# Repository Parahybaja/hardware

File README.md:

# Hardware v2

<p align="center">

</p>

<p align="center">

</p>

## UECU

Universal Electronics Control Unit

## Module

The Accelaration and Velocity test module

### Signal Cleaning

A signal cleaning stage was employed in the digital inputs of each sensor with the aim of eliminating electromagnetic interference in the data transmission line. For this purpose, a passive low-pass filter with a cutoff frequency of 1GHz was implemented.

To achieve the desired cutoff frequency, based on a resistor of *2.2k* ohms, chosen to maintain the optimal current for the optocoupler's LED, the following calculations were made:

$$
F_c = \frac{1}{{2 \pi R C}}
$$

$$
C = \frac{1}{{F_c \cdot 2 \pi R}}
$$

$$
C = \frac{1}{{1 \text{GHz} \cdot 2 \pi \cdot 2.2k}}
$$

$$
C \approx 72 \text{pF}
$$

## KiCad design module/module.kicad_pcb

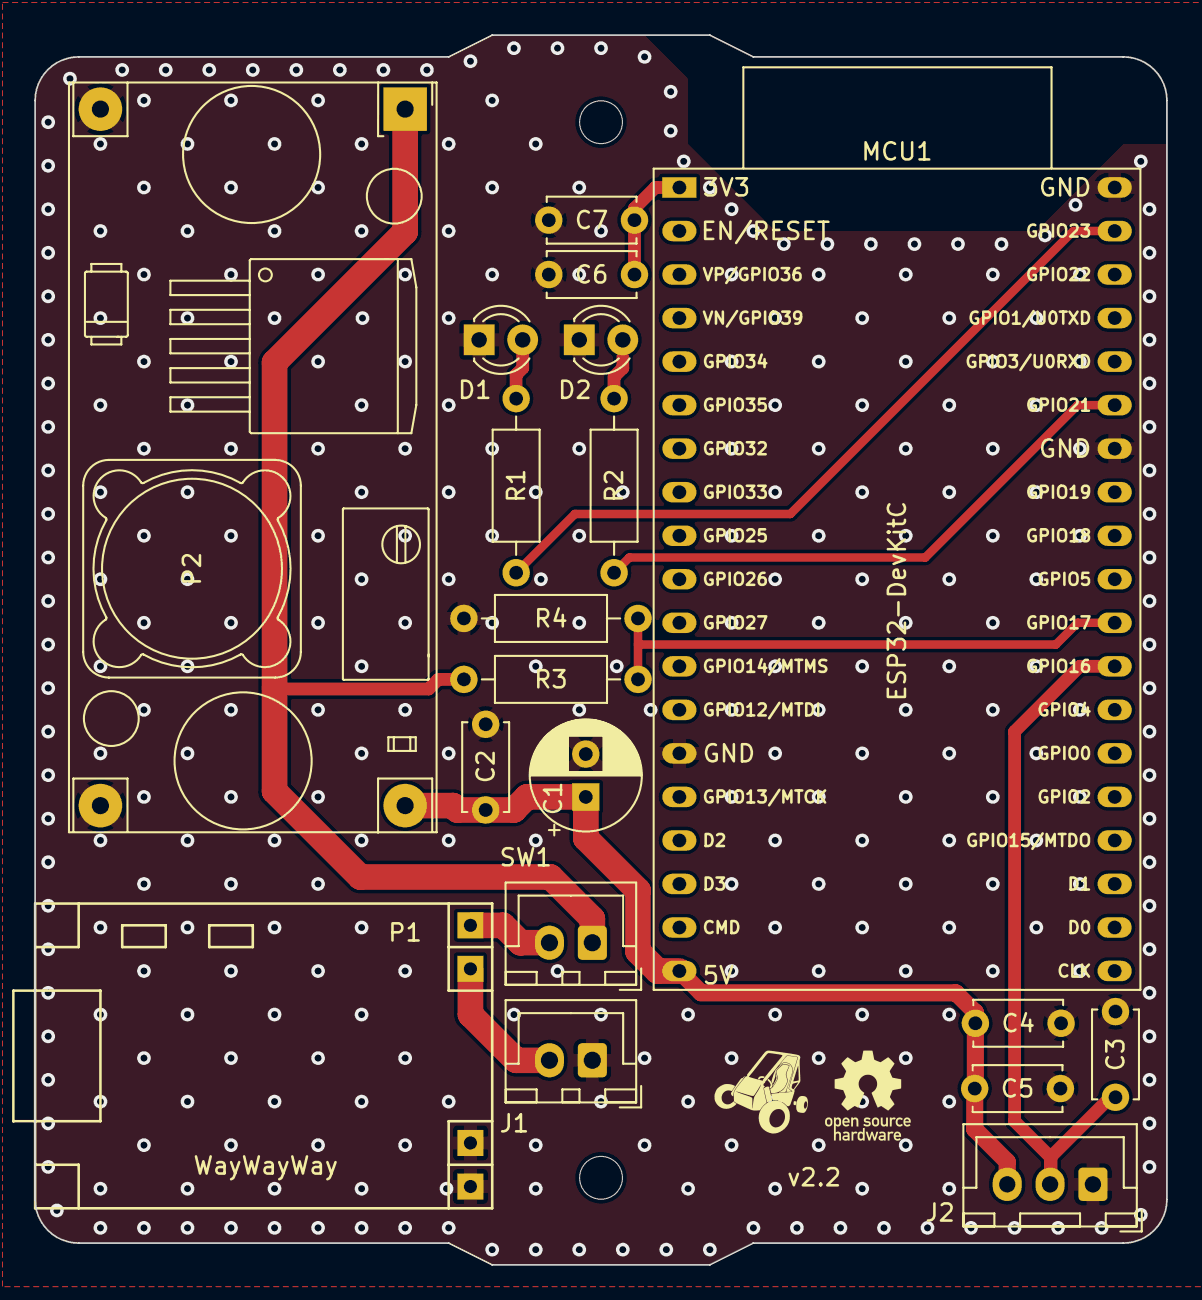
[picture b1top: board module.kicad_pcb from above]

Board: 2 copper layers, 66.0 x 71.8 mm, 23 parts (0 on the bottom side), 12 nets.

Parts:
C1: 470uF; CP_Radial_D6.3mm_P2.50mm
C2, C5, C7: 100nF; C_Disc_D5.0mm_W2.5mm_P5.00mm
C3: 22pF; C_Disc_D5.0mm_W2.5mm_P5.00mm
C4, C6: 10uF; C_Disc_D5.0mm_W2.5mm_P5.00mm
D1: LEDR; LED_D3.0mm
D2: LEDG; LED_D3.0mm
H1, H2: 3.7; MountingHole_3.7mm
J1: Conn_bat; JST_XH_B2B-XH-A_1x02_P2.50mm_Vertical
J2: Conn_bat; JST_XH_B3B-XH-A_1x03_P2.50mm_Vertical
L1: parahybaja
L2: open_hardware
MCU1: ESP32-DevKitC
P1: TP4056 with protection; TP4056
P2: step up boost; StepDown_LM2596
R1, R2: 300R; R_Axial_DIN0207_L6.3mm_D2.5mm_P10.16mm_Horizontal
R3, R4: R_Small; R_Axial_DIN0207_L6.3mm_D2.5mm_P10.16mm_Horizontal
SW1: Conn_sw; JST_XH_B2B-XH-A_1x02_P2.50mm_Vertical

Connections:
+3V3: C6.1, C7.1, MCU1.1 (3V3)
+5V: C1.1, C2.1, C4.1, C5.1, J2.3, MCU1.19 (5V), P2.4 (Vout)
GND: C1.2, C2.2, C3.2, C4.2, C5.2, C6.2, C7.2, D1.1 (K), D2.1 (K), J1.1, J2.1, MCU1.14 (GND), MCU1.32 (GND), MCU1.38 (GND), P1.3 (B-), P1.4 (OUT-), P2.2 (GND), P2.3 (GND), R4.2
LED_ALIVE: MCU1.37 (GPIO23), R1.1
LED_ON: MCU1.33 (GPIO21), R2.1
unnamed: D1.2 (A), R1.2
unnamed: D2.2 (A), R2.2
unnamed: J1.2, P1.2 (B+)
unnamed: P1.1 (OUT+), SW1.2 (B)
VBat: P2.1 (Vin), R3.1, SW1.1 (A)
VOLTAGE_DIVIDER: MCU1.28 (GPIO17), R3.2, R4.1
signal: C3.1, J2.2, MCU1.27 (GPIO16)

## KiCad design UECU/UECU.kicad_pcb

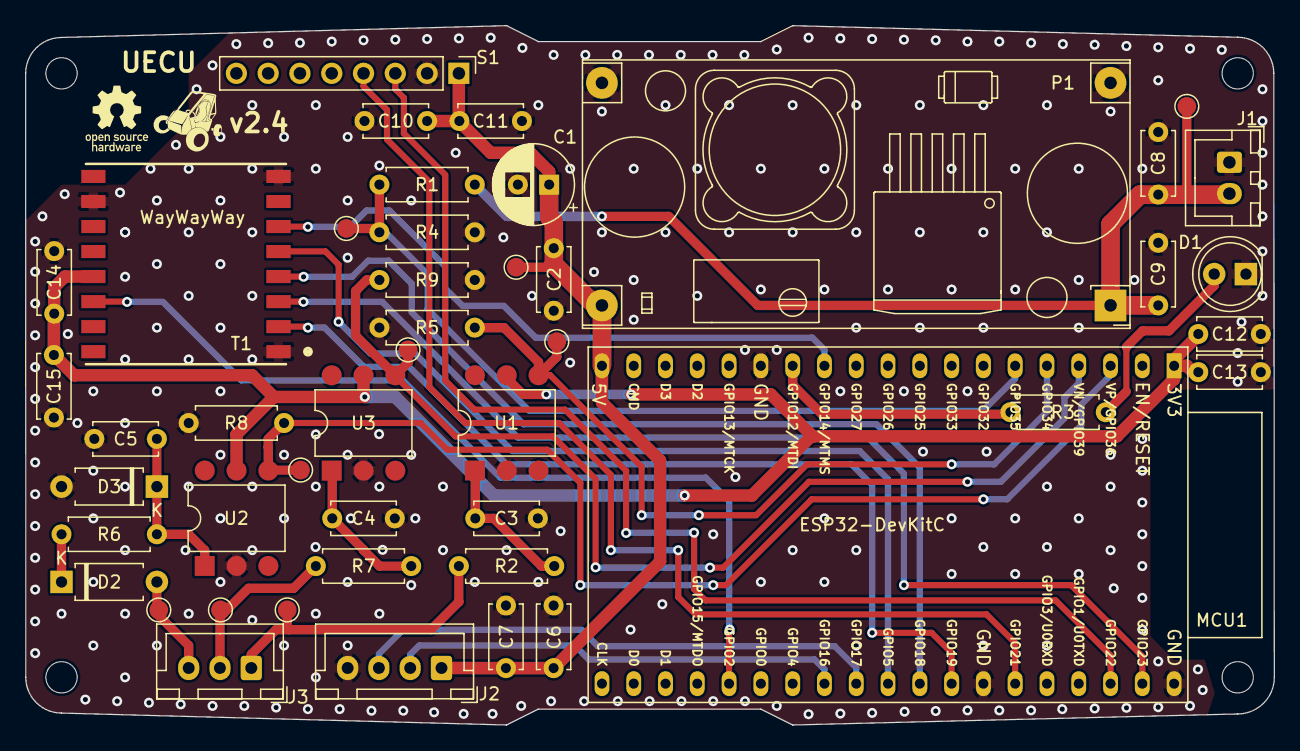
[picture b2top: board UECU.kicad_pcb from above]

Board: 2 copper layers, 99.8 x 55.9 mm, 44 parts (0 on the bottom side), 27 nets.

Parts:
C1: 470uF; CP_Radial_D6.3mm_P2.50mm
C2, C7, C9, C11, C13, C15: 100nF; C_Disc_D5.0mm_W2.5mm_P5.00mm
C3, C4, C5: 10pF; C_Disc_D5.0mm_W2.5mm_P5.00mm
C6, C8, C10, C12, C14: 10uF; C_Disc_D5.0mm_W2.5mm_P5.00mm
D1: LED; LED_D5.0mm
D2: 1N4007; D_A-405_P7.62mm_Horizontal
D3: ZENER 3V3; D_A-405_P7.62mm_Horizontal
H1, H2, H3, H4: 3.7; MountingHole_3.7mm
J1: Conn_pwr; JST_XH_B2B-XH-A_1x02_P2.50mm_Vertical
J2: Conn_display; JST_XH_B4B-XH-A_1x04_P2.50mm_Vertical
J3: Conn_SENSORS; JST_XH_B3B-XH-A_1x03_P2.50mm_Vertical
L1: parahybaja
L2: open_hardware
MCU1: ESP32-DevKitC
P1: LM2596_buck; StepDown_LM2596
R1, R5, R8, R9: 10k; R_Axial_DIN0207_L6.3mm_D2.5mm_P7.62mm_Horizontal
R2, R7: 2k; R_Axial_DIN0207_L6.3mm_D2.5mm_P7.62mm_Horizontal
R3: 470R; R_Axial_DIN0207_L6.3mm_D2.5mm_P7.62mm_Horizontal
R4: 2k2; R_Axial_DIN0207_L6.3mm_D2.5mm_P7.62mm_Horizontal
R6: 59k; R_Axial_DIN0207_L6.3mm_D2.5mm_P7.62mm_Horizontal
REFe: TestPoint_Pad_D1.5mm
S1: PinHeader_1x08_P2.54mm_Vertical
T1: LoRa-SX1276; LoRa_SX1276
U1, U2, U3: 4N25; DIP-6_W7.62mm

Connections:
+3V3: C12.1, C13.1, C14.1, C15.1, MCU1.1 (3V3), T1.13 (3_3V), U1.5, U2.5, U3.5
+5V: C1.1, C2.1, C6.1, C7.1, C10.1, C11.1, J2.1, MCU1.19 (5V), P1.4 (Vout), S1.1 (VCC)
+12V: C8.1, C9.1, J1.2, P1.1 (Vin), R1.1
CONN_EMG: J3.1, R2.1
CONN_RPM: D2.2 (A), J3.3
CONN_SPD: J3.2, R7.1, REFe.1
DIO: MCU1.24 (*GPIO2/ADC2_CH2), T1.14 (DIO0)
GND: C1.2, C2.2, C3.2, C4.2, C5.2, C6.2, C7.2, C8.2, C9.2, C10.2, C11.2, C12.2, C13.2, C14.2, C15.2, D1.1 (K), D3.2 (A), J1.1, J2.4, MCU1.14 (GND), MCU1.32 (GND), MCU1.38 (GND), P1.2 (GND), P1.3 (GND), R4.2, R5.2, R8.2, R9.2, S1.2 (GND), T1.1 (GND), T1.8 (GND), T1.10 (GND), U1.2, U2.2, U3.2
LED_ALIVE: MCU1.13 (VDD_FLASH/GPIO12/*MTDI/ADC2_CH5), R3.1
MISO: MCU1.31 (GPIO19), T1.2 (MISO)
MOSI: MCU1.37 (GPIO23), T1.3 (MOSI)
NSS: MCU1.29 (SDIO/*GPIO5), T1.5 (NSS)
unnamed: C3.1, R2.2, U1.1
unnamed: C4.1, R7.2, U3.1
unnamed: D1.2 (A), R3.2
unnamed: D2.1 (K), R6.1
unnamed: C5.1, D3.1 (K), R6.2, U2.1
RST: MCU1.12 (GPIO14/MTMS/ADC2_CH6), T1.6 (RESET)
RXD2: J2.2, MCU1.27 (GPIO16)
SCK: MCU1.30 (GPIO18), T1.4 (SCK)
SCL: MCU1.36 (GPIO22), S1.3 (SCL)
SDA: MCU1.33 (GPIO21), S1.4 (SDA)
SIGNAL_EMG: MCU1.5 (GPIO34/VDET_1/ADC1_CH6), R5.1, U1.4
SIGNAL_RPM: MCU1.3 (GPIO36/SENSOR_VP/ADC1_CH0), R8.1, U2.4
SIGNAL_SPD: MCU1.4 (GPIO39/SENSOR_VN/ADC1_CH3), R9.1, U3.4
TXD2: J2.3, MCU1.28 (GPIO17)
VBAT-3V: MCU1.6 (GPIO35/VDET_2/ADC1_CH7), R1.2, R4.1

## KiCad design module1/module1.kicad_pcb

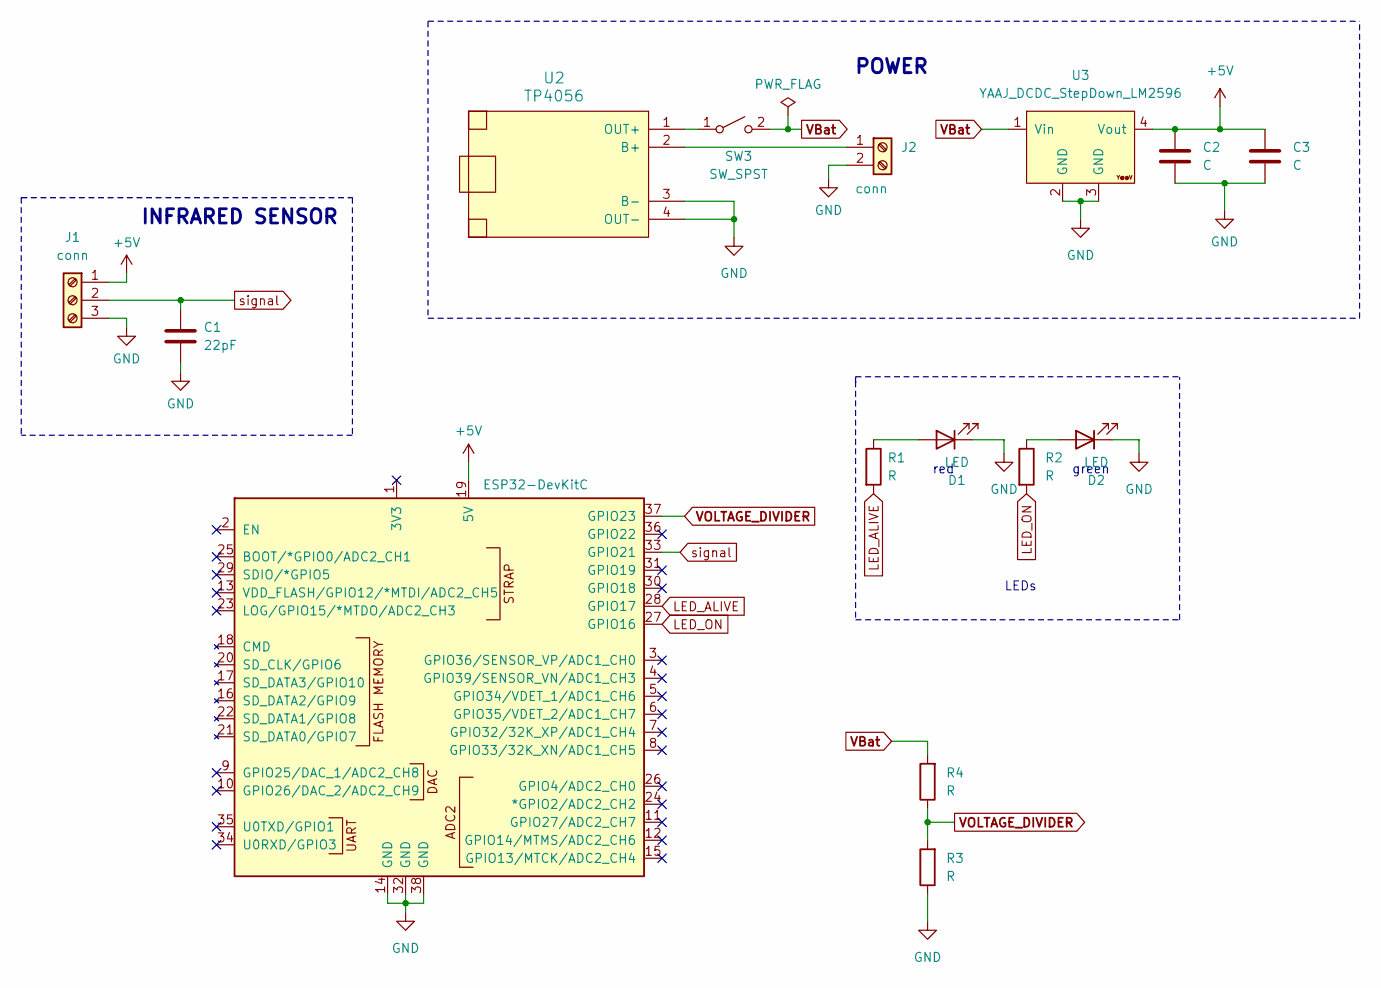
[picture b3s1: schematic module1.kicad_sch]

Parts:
C1: 22pF; C_Disc_D3.0mm_W1.6mm_P2.50mm
C2, C3: C; C_Disc_D3.0mm_W1.6mm_P2.50mm
D1, D2: LED; LED_D3.0mm
J1: conn; TerminalBlock_bornier-3_P5.08mm
J2: conn; TerminalBlock_bornier-2_P5.08mm
R1, R2, R3, R4: R; R_Axial_DIN0207_L6.3mm_D2.5mm_P10.16mm_Horizontal
SW3: SW_SPST; TerminalBlock_bornier-2_P5.08mm
U1: ESP32-DevKitC
U2: TP4056
U3: YAAJ_DCDC_StepDown_LM2596; StepDown_LM2596

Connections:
+5V: C2.1, C3.1, J1.1, U1.19 (5V), U3.4 (Vout)
GND: C1.2, C2.2, C3.2, D1.1 (K), D2.1 (K), J1.3, J2.2, R3.1, U1.14 (GND), U1.32 (GND), U1.38 (GND), U2.3 (B-), U2.4 (OUT-), U3.2 (GND), U3.3 (GND)
LED_ALIVE: R1.2, U1.28 (GPIO17)
LED_ON: R2.2, U1.27 (GPIO16)
unnamed: D1.2 (A), R1.1
unnamed: D2.2 (A), R2.1
unnamed: J2.1, U2.2 (B+)
unnamed: SW3.1 (A), U2.1 (OUT+)
VBat: R4.2, SW3.2 (B), U3.1 (Vin)
VOLTAGE_DIVIDER: R3.2, R4.1, U1.37 (GPIO23)
signal: C1.1, J1.2, U1.33 (GPIO21)

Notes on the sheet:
INFRARED SENSOR
LEDs
red
POWER
green

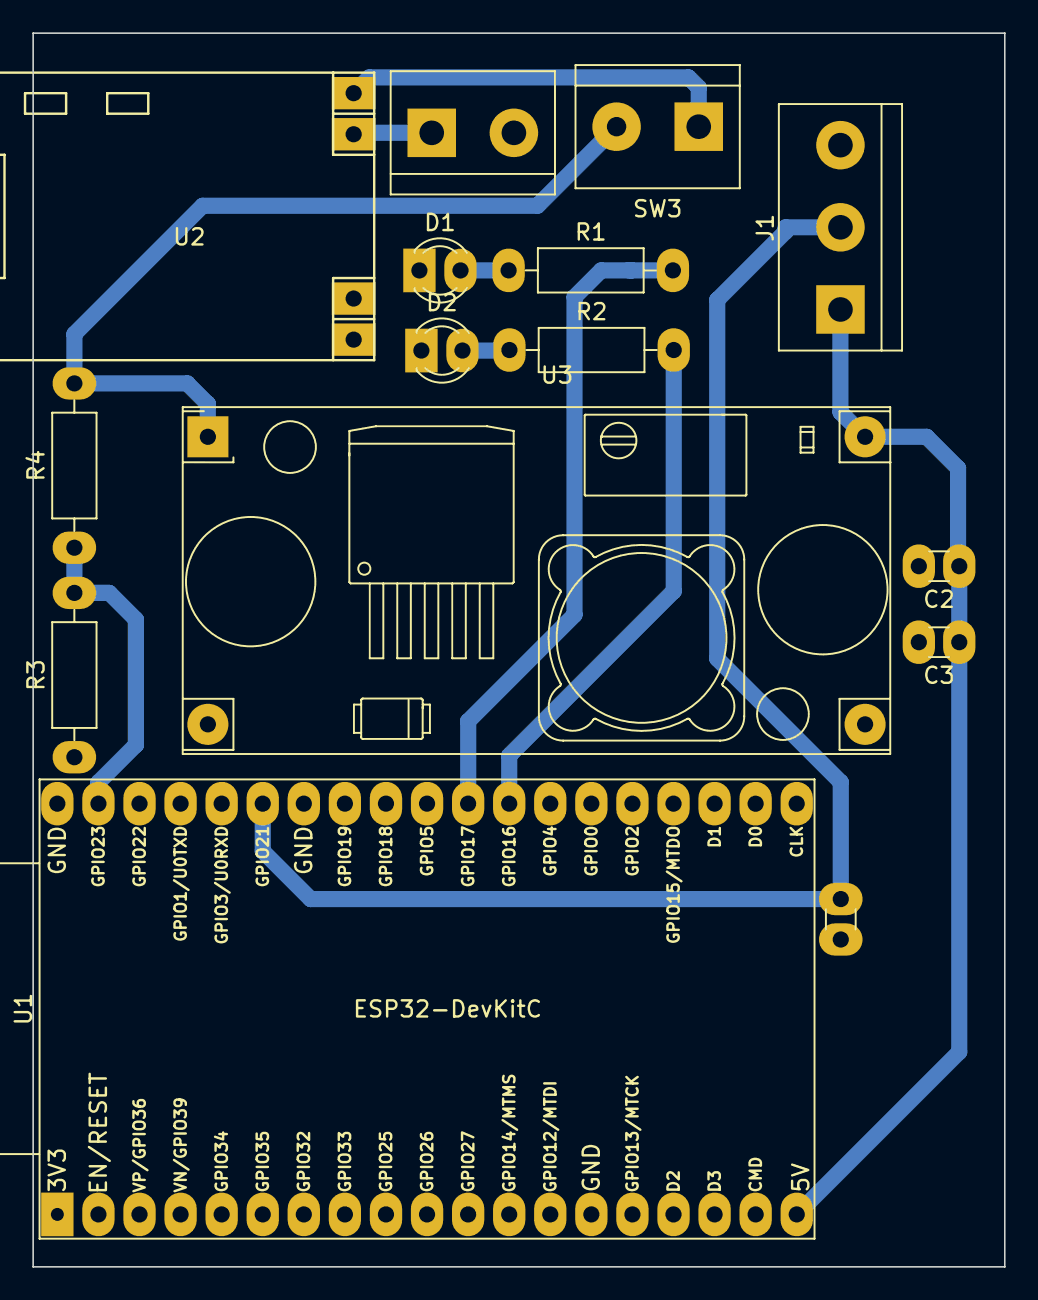
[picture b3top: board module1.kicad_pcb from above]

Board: 2 copper layers, 60.1 x 76.3 mm, 16 parts (1 on the bottom side), 11 nets.

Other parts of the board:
e: LOGO; logocarro

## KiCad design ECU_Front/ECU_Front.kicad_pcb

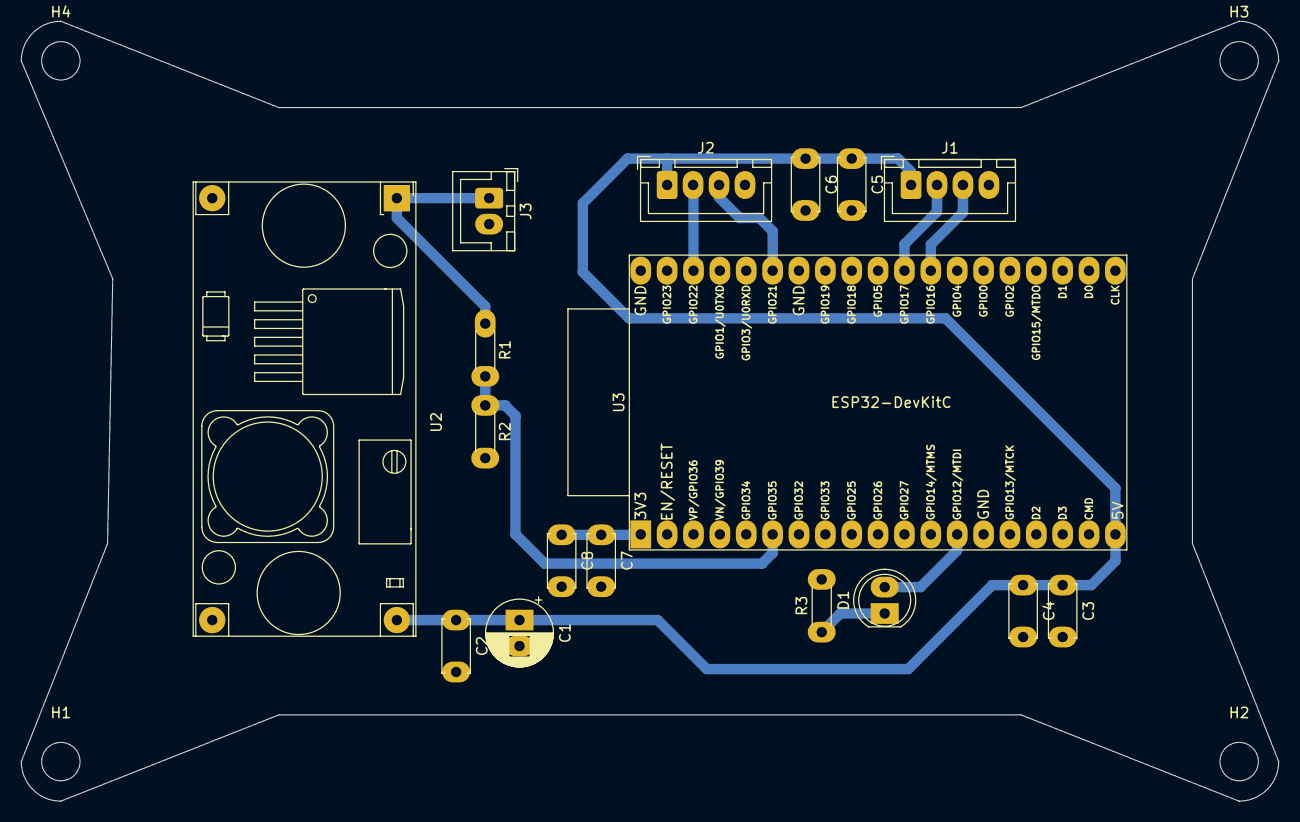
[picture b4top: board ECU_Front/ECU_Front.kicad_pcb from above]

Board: 2 copper layers, 121.1 x 75.1 mm, 21 parts (0 on the bottom side), 11 nets.

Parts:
C1: 470uF; CP_Radial_D6.3mm_P2.50mm
C2, C4, C6, C8: 100nF; C_Disc_D5.0mm_W2.5mm_P5.00mm
C3, C5, C7: 10uF; C_Disc_D5.0mm_W2.5mm_P5.00mm
D1: LED; LED_D5.0mm
H1, H2, H3, H4: 3.7; MountingHole_3.7mm
J1: Conn_display; JST_XH_B4B-XH-A_1x04_P2.50mm_Vertical
J2: Conn_acc; JST_XH_B4B-XH-A_1x04_P2.50mm_Vertical
J3: Conn_pwr; JST_XH_B2B-XH-A_1x02_P2.50mm_Vertical
R1: 10k; R_Axial_DIN0204_L3.6mm_D1.6mm_P5.08mm_Horizontal
R2: 2k2; R_Axial_DIN0204_L3.6mm_D1.6mm_P5.08mm_Horizontal
R3: 470R; R_Axial_DIN0204_L3.6mm_D1.6mm_P5.08mm_Horizontal
U2: LM2596_buck; StepDown_LM2596
U3: ESP32-DevKitC

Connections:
+3V3: C7.1, C8.1, U3.1 (3V3)
+5V: C1.1, C2.1, C3.1, C4.1, C5.1, C6.1, J1.1, J2.1, U2.4 (Vout), U3.19 (5V)
+12V: J3.1, R1.1, U2.1 (Vin)
GND: C1.2, C2.2, C3.2, C4.2, C5.2, C6.2, C7.2, C8.2, J1.4, J2.4, J3.2, R2.2, R3.2, U2.2 (GND), U2.3 (GND), U3.14 (GND), U3.32 (GND), U3.38 (GND)
LED_ALIVE: D1.2 (A), U3.13 (VDD_FLASH/GPIO12/*MTDI/ADC2_CH5)
unnamed: D1.1 (K), R3.1
RXD2: J1.3, U3.27 (GPIO16)
SCL: J2.2, U3.36 (GPIO22)
SDA: J2.3, U3.33 (GPIO21)
TXD2: J1.2, U3.28 (GPIO17)
VBAT-3V: R1.2, R2.1, U3.6 (GPIO35/VDET_2/ADC1_CH7)

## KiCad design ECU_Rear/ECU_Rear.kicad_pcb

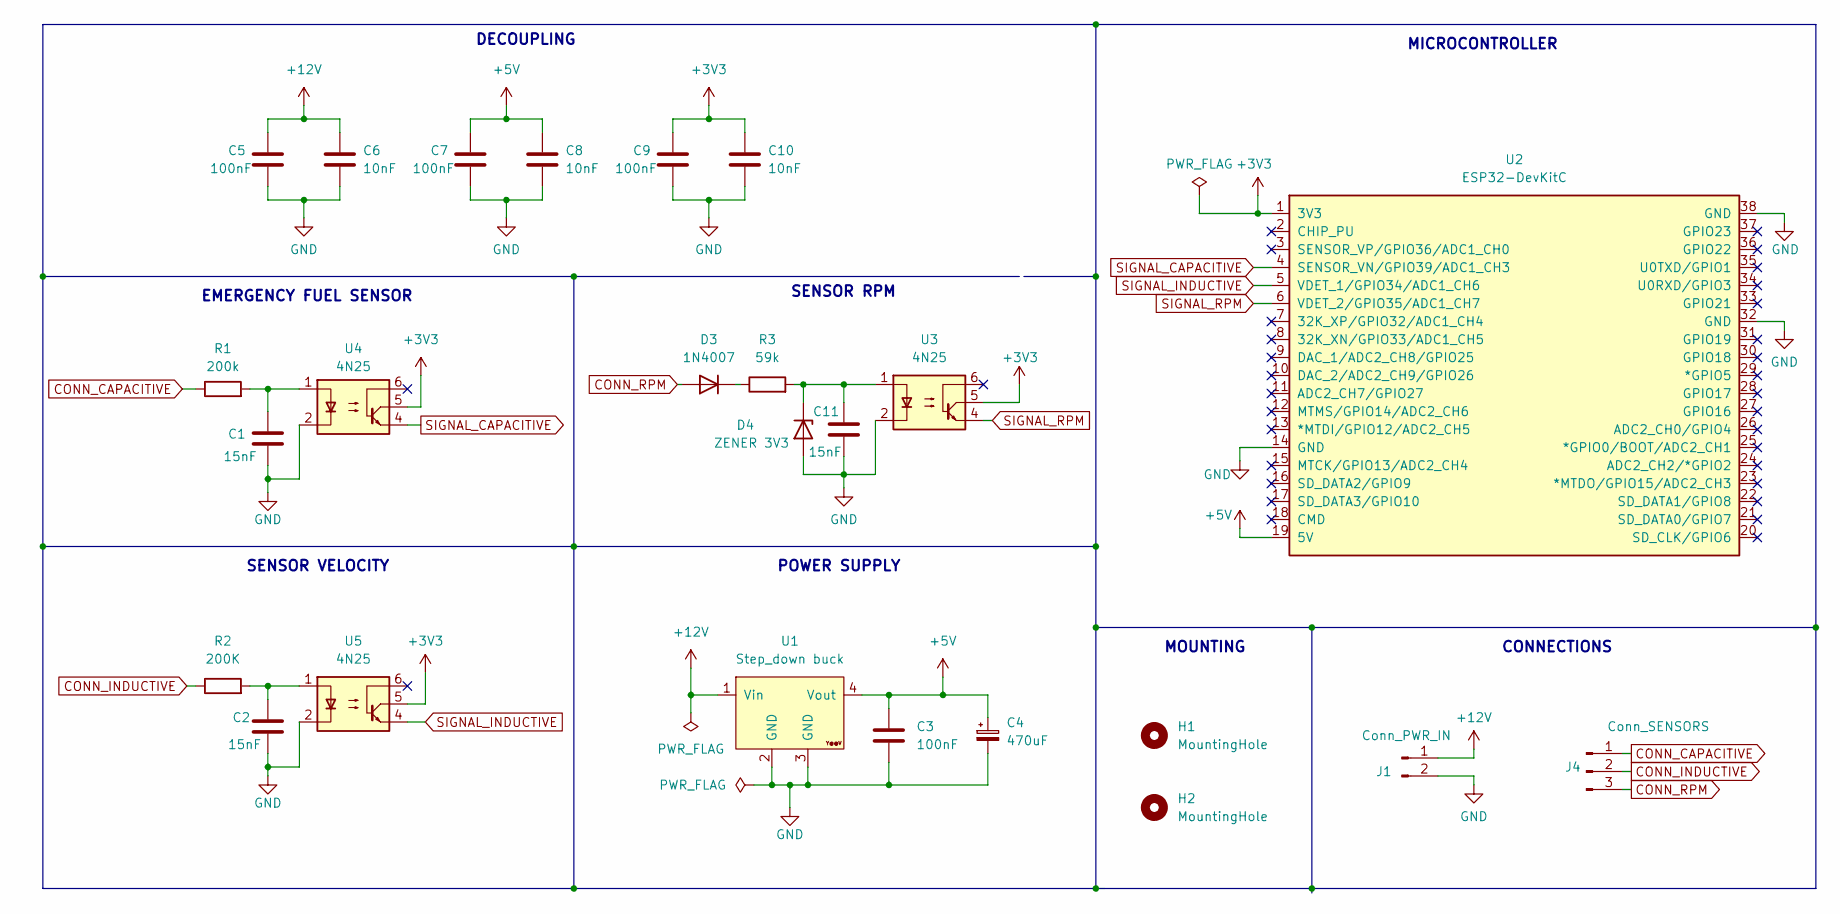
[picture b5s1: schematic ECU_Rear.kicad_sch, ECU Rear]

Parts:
C1, C2, C11: 15nF; C_Disc_D5.0mm_W2.5mm_P5.00mm
C3, C5, C7, C9: 100nF; C_Disc_D5.0mm_W2.5mm_P5.00mm
C4: 470uF; CP_Radial_D6.3mm_P2.50mm
C6, C8, C10: 10nF; C_Disc_D5.0mm_W2.5mm_P5.00mm
D3: 1N4007; D_A-405_P7.62mm_Horizontal
D4: ZENER 3V3; D_A-405_P7.62mm_Horizontal
H1, H2: MountingHole; MountingHole_4.3mm_M4
J1: Conn_PWR_IN; PinHeader_1x02_P2.54mm_Vertical
J4: Conn_SENSORS; PinHeader_1x03_P2.54mm_Vertical
R1: 200k; R_Axial_DIN0204_L3.6mm_D1.6mm_P5.08mm_Horizontal
R2: 200K; R_Axial_DIN0204_L3.6mm_D1.6mm_P5.08mm_Horizontal
R3: 59k; R_Axial_DIN0204_L3.6mm_D1.6mm_P5.08mm_Horizontal
U1: Step_down buck; StepDown_LM2596
U2: ESP32-DevKitC
U3, U4, U5: 4N25; DIP-6_W7.62mm

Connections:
+3V3: C9.1, C10.1, U2.1 (3V3), U3.5, U4.5, U5.5
+5V: C3.1, C4.1, C7.1, C8.1, U1.4 (Vout), U2.19 (5V)
+12V: C5.1, C6.1, J1.1, U1.1 (Vin)
CONN_CAPACITIVE: J4.1, R1.1
CONN_INDUCTIVE: J4.2, R2.1
CONN_RPM: D3.2 (A), J4.3
GND: C1.2, C2.2, C3.2, C4.2, C5.2, C6.2, C7.2, C8.2, C9.2, C10.2, C11.2, D4.2 (A), J1.2, U1.2 (GND), U1.3 (GND), U2.14 (GND), U2.32 (GND), U2.38 (GND), U3.2, U4.2, U5.2
unnamed: C1.1, R1.2, U4.1
unnamed: C2.1, R2.2, U5.1
unnamed: D3.1 (K), R3.1
unnamed: C11.1, D4.1 (K), R3.2, U3.1
SIGNAL_CAPACITIVE: U2.4 (SENSOR_VN/GPIO39/ADC1_CH3), U4.4
SIGNAL_INDUCTIVE: U2.5 (VDET_1/GPIO34/ADC1_CH6), U5.4
SIGNAL_RPM: U2.6 (VDET_2/GPIO35/ADC1_CH7), U3.4

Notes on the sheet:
SENSOR RPM
SENSOR VELOCITY
MOUNTING
CONNECTIONS
DECOUPLING
MICROCONTROLLER
POWER SUPPLY
EMERGENCY FUEL SENSOR

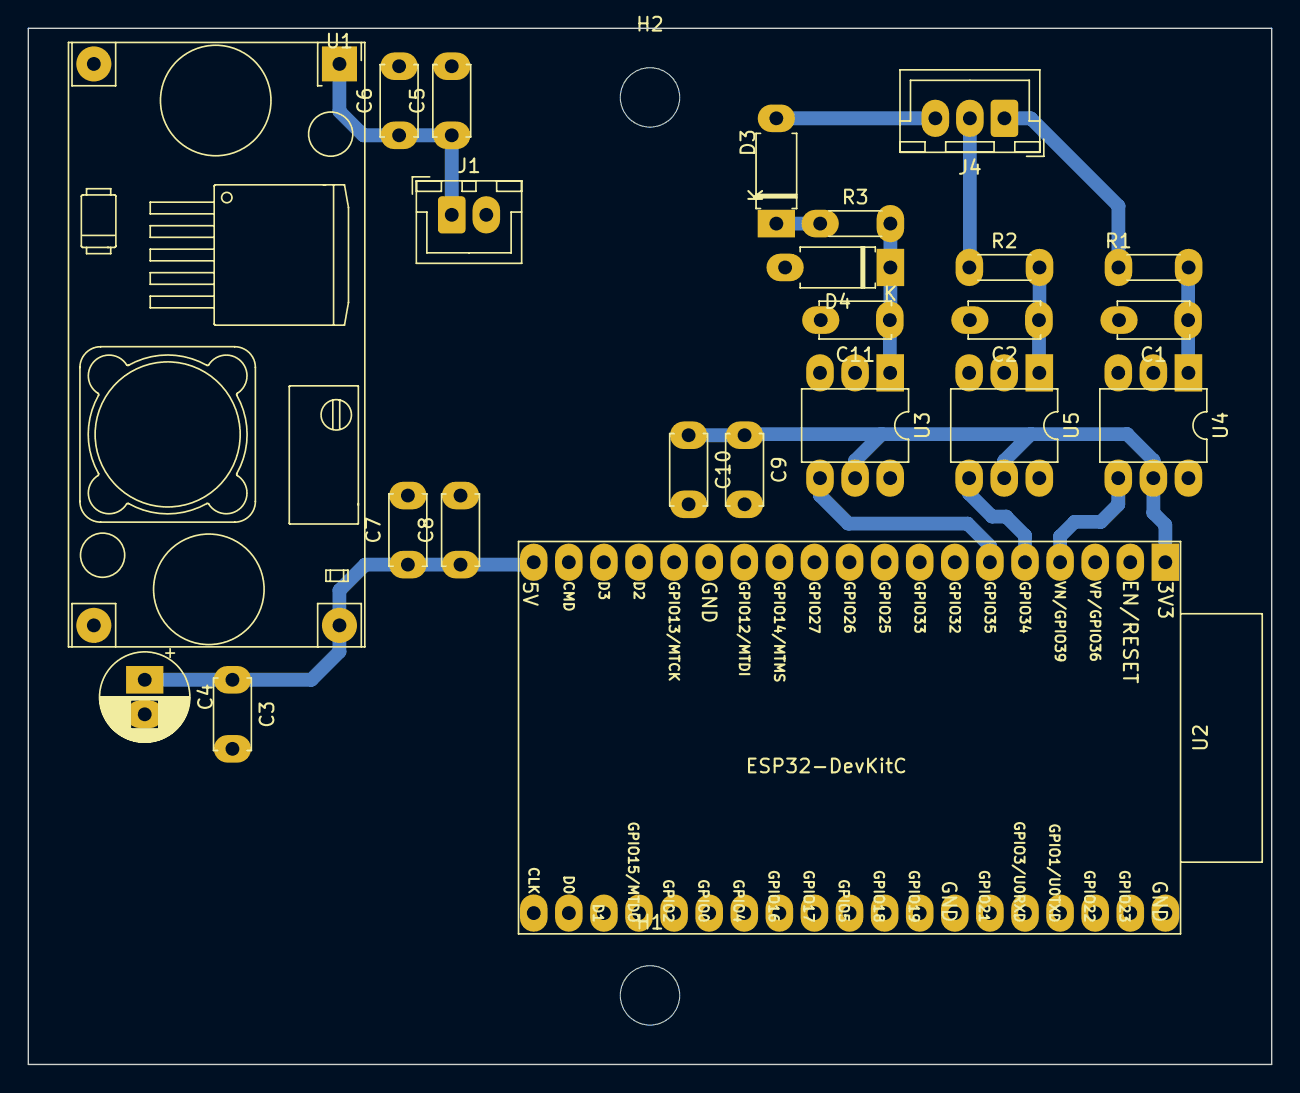
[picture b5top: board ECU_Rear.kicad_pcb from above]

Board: 2 copper layers, 90.0 x 75.0 mm, 25 parts (0 on the bottom side), 14 nets.

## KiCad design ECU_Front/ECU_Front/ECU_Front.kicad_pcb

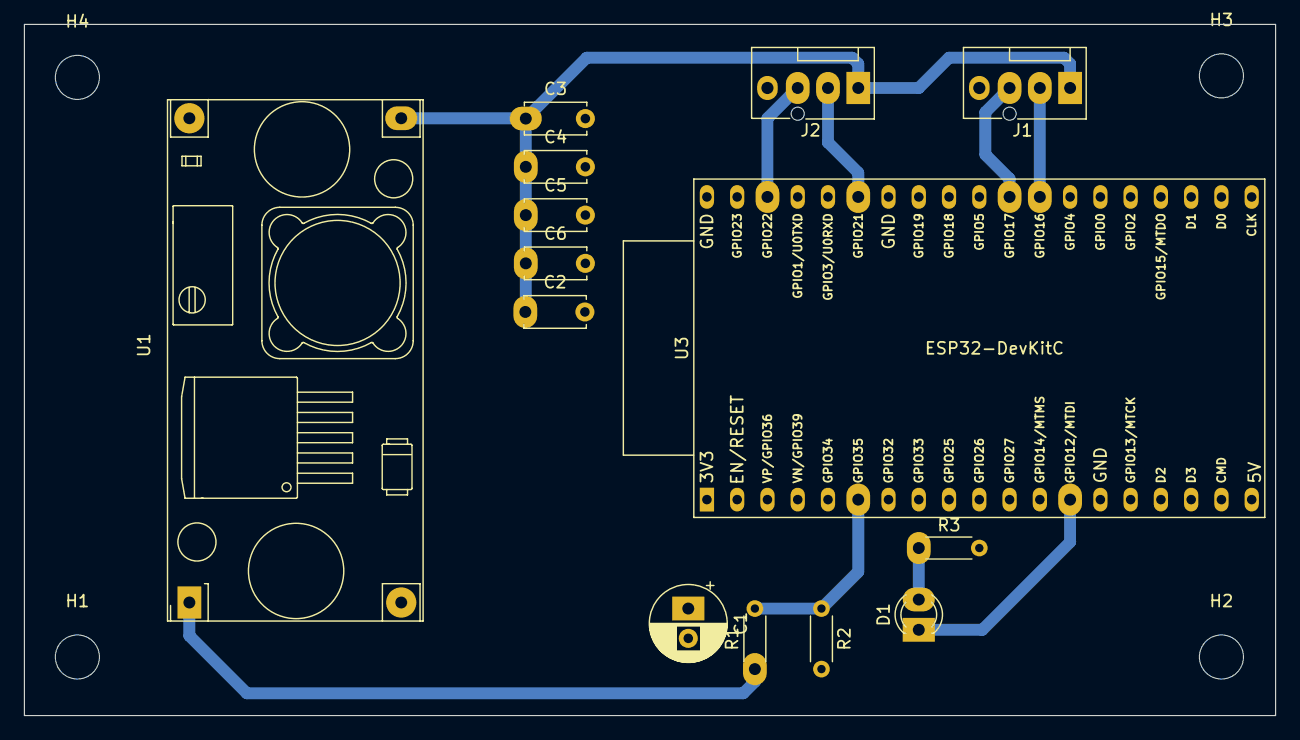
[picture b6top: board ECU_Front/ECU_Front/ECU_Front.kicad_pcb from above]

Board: 2 copper layers, 105.0 x 58.0 mm, 18 parts (0 on the bottom side), 10 nets.

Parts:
C1: 470uF; CP_Radial_D6.3mm_P2.50mm
C2, C4, C6: 100nF; C_Disc_D5.0mm_W2.5mm_P5.00mm
C3, C5: 10uF; C_Disc_D5.0mm_W2.5mm_P5.00mm
D1: LED; LED_D3.0mm_FlatTop
H1, H2, H3, H4: 3.7; MountingHole_3.7mm
J1, J2: Conn_01x04_Pin; FanPinHeader_1x04_P2.54mm_Vertical
R1: 10k; R_Axial_DIN0204_L3.6mm_D1.6mm_P5.08mm_Horizontal
R2: 2k2; R_Axial_DIN0204_L3.6mm_D1.6mm_P5.08mm_Horizontal
R3: 470R; R_Axial_DIN0204_L3.6mm_D1.6mm_P5.08mm_Horizontal
U1: step-down (buck); StepDown_LM2596
U3: ESP32-DevKitC

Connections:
+5V: C1.1, C2.1, C3.1, C4.1, C5.1, C6.1, J1.1, J2.1, U1.3 (Vout), U3.19 (5V)
+12V: R1.1, U1.1 (Vin)
GND: C1.2, C2.2, C3.2, C4.2, C5.2, C6.2, J1.4, J2.4, R2.2, R3.2, U1.2 (GND), U3.32 (GND)
LED_ALIVE: D1.1 (K), U3.13 (VDD_FLASH/GPIO12/*MTDI/ADC2_CH5)
unnamed: D1.2 (A), R3.1
RXD2: J1.2, U3.27 (GPIO16)
SCL: J2.3, U3.36 (GPIO22)
SDA: J2.2, U3.33 (GPIO21)
TXD2: J1.3, U3.28 (GPIO17)
VBAT-3V: R1.2, R2.1, U3.6 (GPIO35/VDET_2/ADC1_CH7)

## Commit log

2023-08-08 First components.
2023-08-10 Cálculos Passa-baixa
    Fiz os cálculos passa-baixa da ECU
2023-08-10 Descrition
    Fiz a descrição do trabalho feito até agora no projeto da placa ECU Rear.
2023-08-12 Esquemático da PCB da ECU rear
    Por favor verificar se estão corretos os valores, principalmente os valores em POWER_SUPPLY dos capacitores e também o símbolo do capacitor polarizado. Encontrei apenas a versão "small". Também verif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
2023-08-12 Adicionei 1 optoacoplador
2023-08-14 Terminei o esquemático, vou começar a placa segunda dia 14/08
2023-08-16 Remove Auto_save_files
2023-08-16 adicionei os aptoacopladores aos circuitos dos sensores da PCB
    .
2023-08-17 Esquemático e Desenho da placa
    Fiz modificações nos Decoupling. Colocando os números corretos de componentes e próximos às saídas de energia. Iniciei o desenho da placa levando em consideração as dimensões da caixa e a melhor posi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
2023-08-20 fiz schematic and remake layout
2023-09-29 ECU_DISPLAY First project
2023-09-30 Consertei os problemas nos furos e na posição do holes.
2023-09-30 ECU_Front, definitive edition
2023-10-01 ECU_Front definitive edition 2
    Consertei o problema das pastas.
2023-10-07 final fix ECU Front
2023-10-07 update ECU Rear
2023-10-07 create machining path
2023-10-07 change holes
2023-11-03 add module 1
2023-12-26 create components folder
2023-12-26 create UECU schematic
2023-12-28 add front layer
2023-12-28 finish bottom layer
2023-12-28 add ground vias
2023-12-29 create new module
2023-12-29 cleaning repo
2024-03-03 add new lora 3d model
2024-03-03 add renders
2025-12-18 New version of the ECU
    Now we can use more efficiently all pins, the design is focused on implementing the CAN Module and ambiguous wiring.
